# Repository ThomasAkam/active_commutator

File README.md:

# Active commutator

A simple open source active commutator for Open Ephys / Intan electrophysiology systems.  Uses a hall sensor and magnet to detect rotation of the cable,  a slip ring powered by a continuous rotation servo to correct it, controlled by an Adafruit Trinket M0  running Circuitpython. 

Inspired by earlier designs from [Liberti et al. 2017](https://iopscience.iop.org/article/10.1088/1741-2552/aa6806/meta) and [Fee and Leonardo 2001](https://www.sciencedirect.com/science/article/pii/S0165027001004265).

## Wiring diagram

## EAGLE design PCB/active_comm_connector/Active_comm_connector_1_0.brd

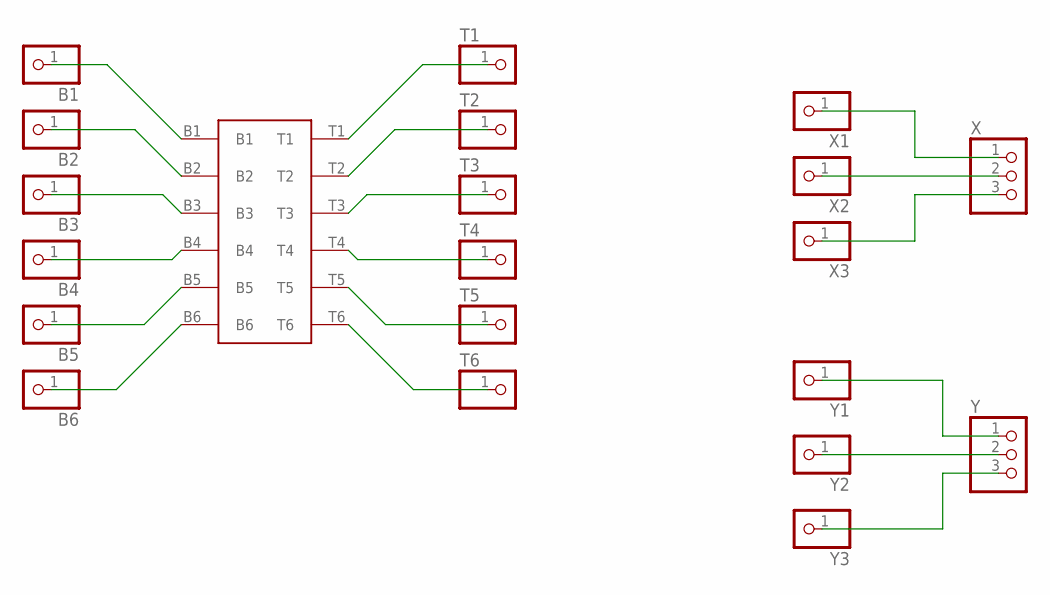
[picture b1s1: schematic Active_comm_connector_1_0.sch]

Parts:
B1, B2, B3, B4, B5, B6: PINHD-1X1; 1X01
PZN-12-VV: PZN-12-VV; OMNETICS_PZN-12-VV
T1, T2, T3, T4, T5, T6: PINHD-1X1; 1X01
X: PINHD-1X3; 1X03
X1, X2, X3: PINHD-1X1; 1X01
Y: PINHD-1X3; 1X03
Y1, Y2, Y3: PINHD-1X1; 1X01

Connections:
B4: B4.1, PZN-12-VV.B4
unnamed: B1.1, PZN-12-VV.B1
unnamed: B2.1, PZN-12-VV.B2
unnamed: B3.1, PZN-12-VV.B3
unnamed: Y.1, Y1.1
unnamed: B5.1, PZN-12-VV.B5
unnamed: B6.1, PZN-12-VV.B6
unnamed: PZN-12-VV.T1, T1.1
unnamed: PZN-12-VV.T2, T2.1
unnamed: PZN-12-VV.T3, T3.1
unnamed: PZN-12-VV.T4, T4.1
unnamed: PZN-12-VV.T5, T5.1
unnamed: PZN-12-VV.T6, T6.1
unnamed: Y.2, Y2.1
unnamed: Y.3, Y3.1
unnamed: X.2, X2.1
unnamed: X.3, X3.1
XX1: X.1, X1.1

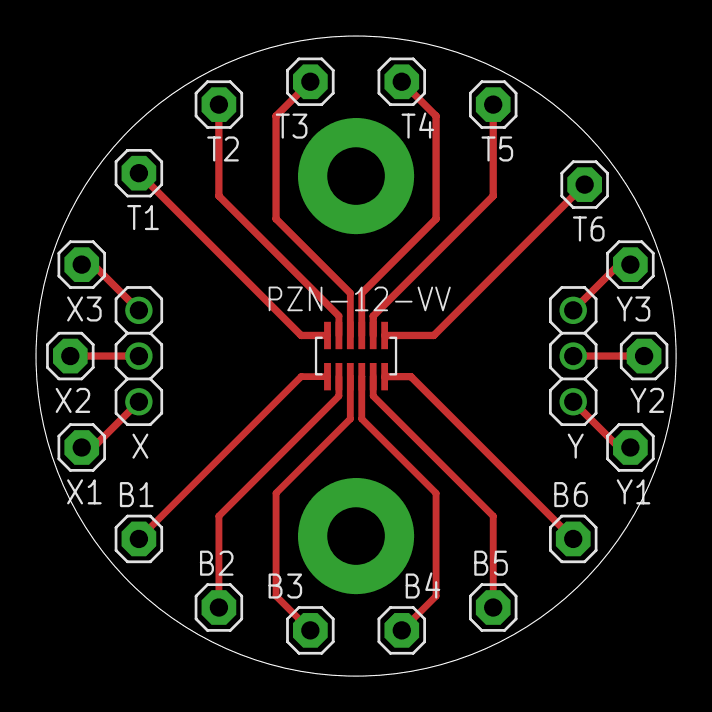
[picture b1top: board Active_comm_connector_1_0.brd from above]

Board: 2 copper layers, 35.6 x 35.6 mm, 21 parts (0 on the bottom side), 18 nets.

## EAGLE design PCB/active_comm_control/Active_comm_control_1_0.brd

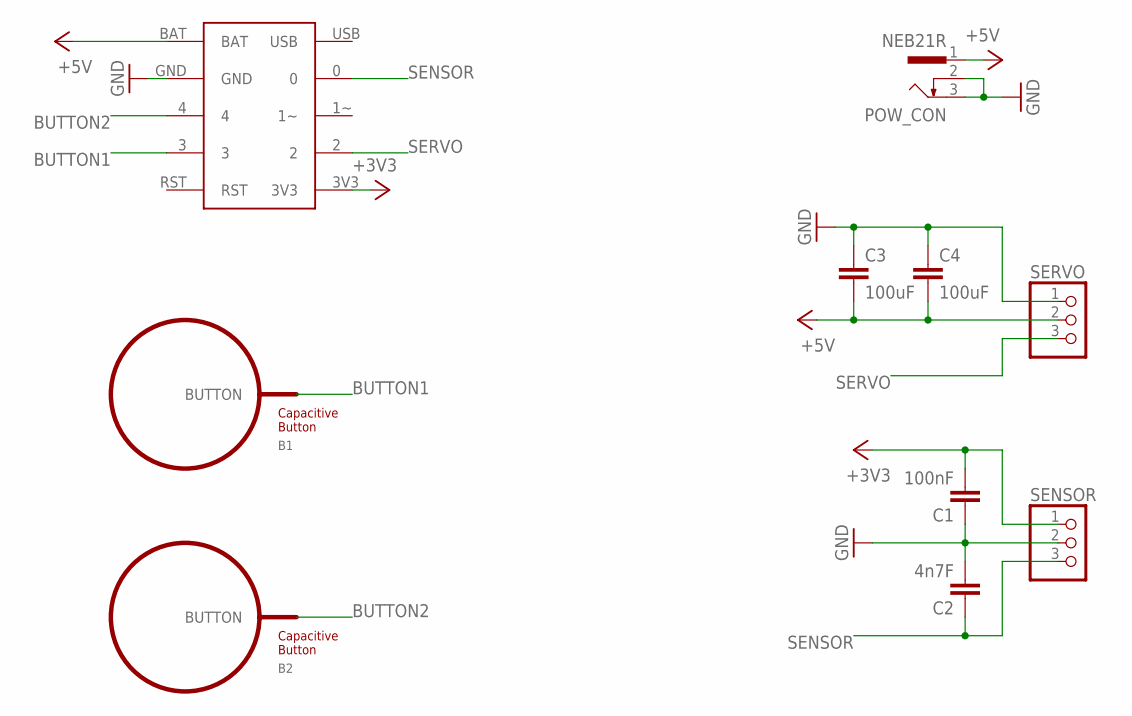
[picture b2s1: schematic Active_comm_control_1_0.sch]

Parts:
B1, B2: BUTTON_PASSIVE10MM; BUTTON_PASSIVE_10MM
C1: 100nF; C0805
C2: 4n7F; C0805
C3, C4: 100uF; C1206
POW_CON: NEB21R
SENSOR: PINHD-1X3; 1X03
SERVO: PINHD-1X3; 1X03
TRINKET-M0: TRINKET-M0; TRINKET-M0-NO-HOLES

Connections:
+3V3: C1.2, SENSOR.1, TRINKET-M0.3V3
+5V: C3.2, C4.2, POW_CON.1, SERVO.2, TRINKET-M0.BAT
BUTTON1: B1.BUTTON, TRINKET-M0.3
BUTTON2: B2.BUTTON, TRINKET-M0.4
GND: C1.1, C2.2, C3.1, C4.1, POW_CON.2, POW_CON.3, SENSOR.2, SERVO.1, TRINKET-M0.GND
SENSOR: C2.1, SENSOR.3, TRINKET-M0.0
SERVO: SERVO.3, TRINKET-M0.2

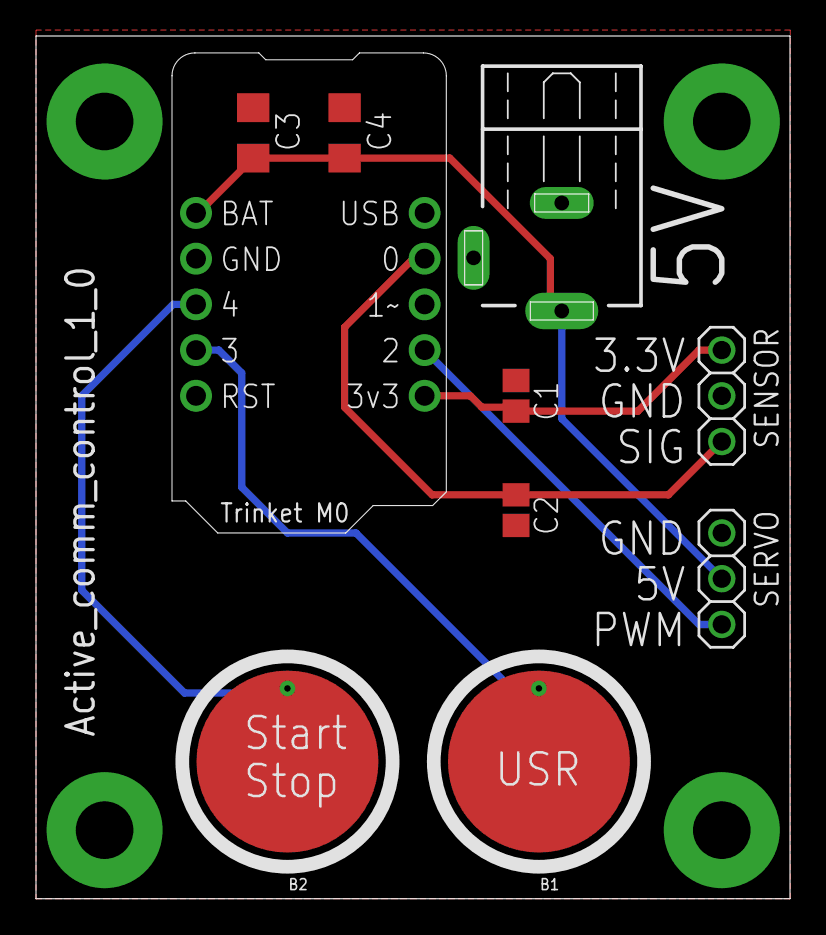
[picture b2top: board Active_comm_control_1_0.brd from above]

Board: 2 copper layers, 41.9 x 47.9 mm, 10 parts (0 on the bottom side), 7 nets.

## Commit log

2022-04-04 - Initial commit
2024-05-31 - Updated code to start in "running" state, print info regularly during run, and have different threshold for starting and stopping motion.
2024-05-31 Added wiring diagram to readme

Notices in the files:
parts and their libraries:
TouchWidgets: License : http://creativecommons.org/licenses/by-sa/4.0/ (Creative Commons 4.0)
TouchWidgets: License : http://creativecommons.org/licenses/by-sa/3.1/ (Creative Commons 3.1)
